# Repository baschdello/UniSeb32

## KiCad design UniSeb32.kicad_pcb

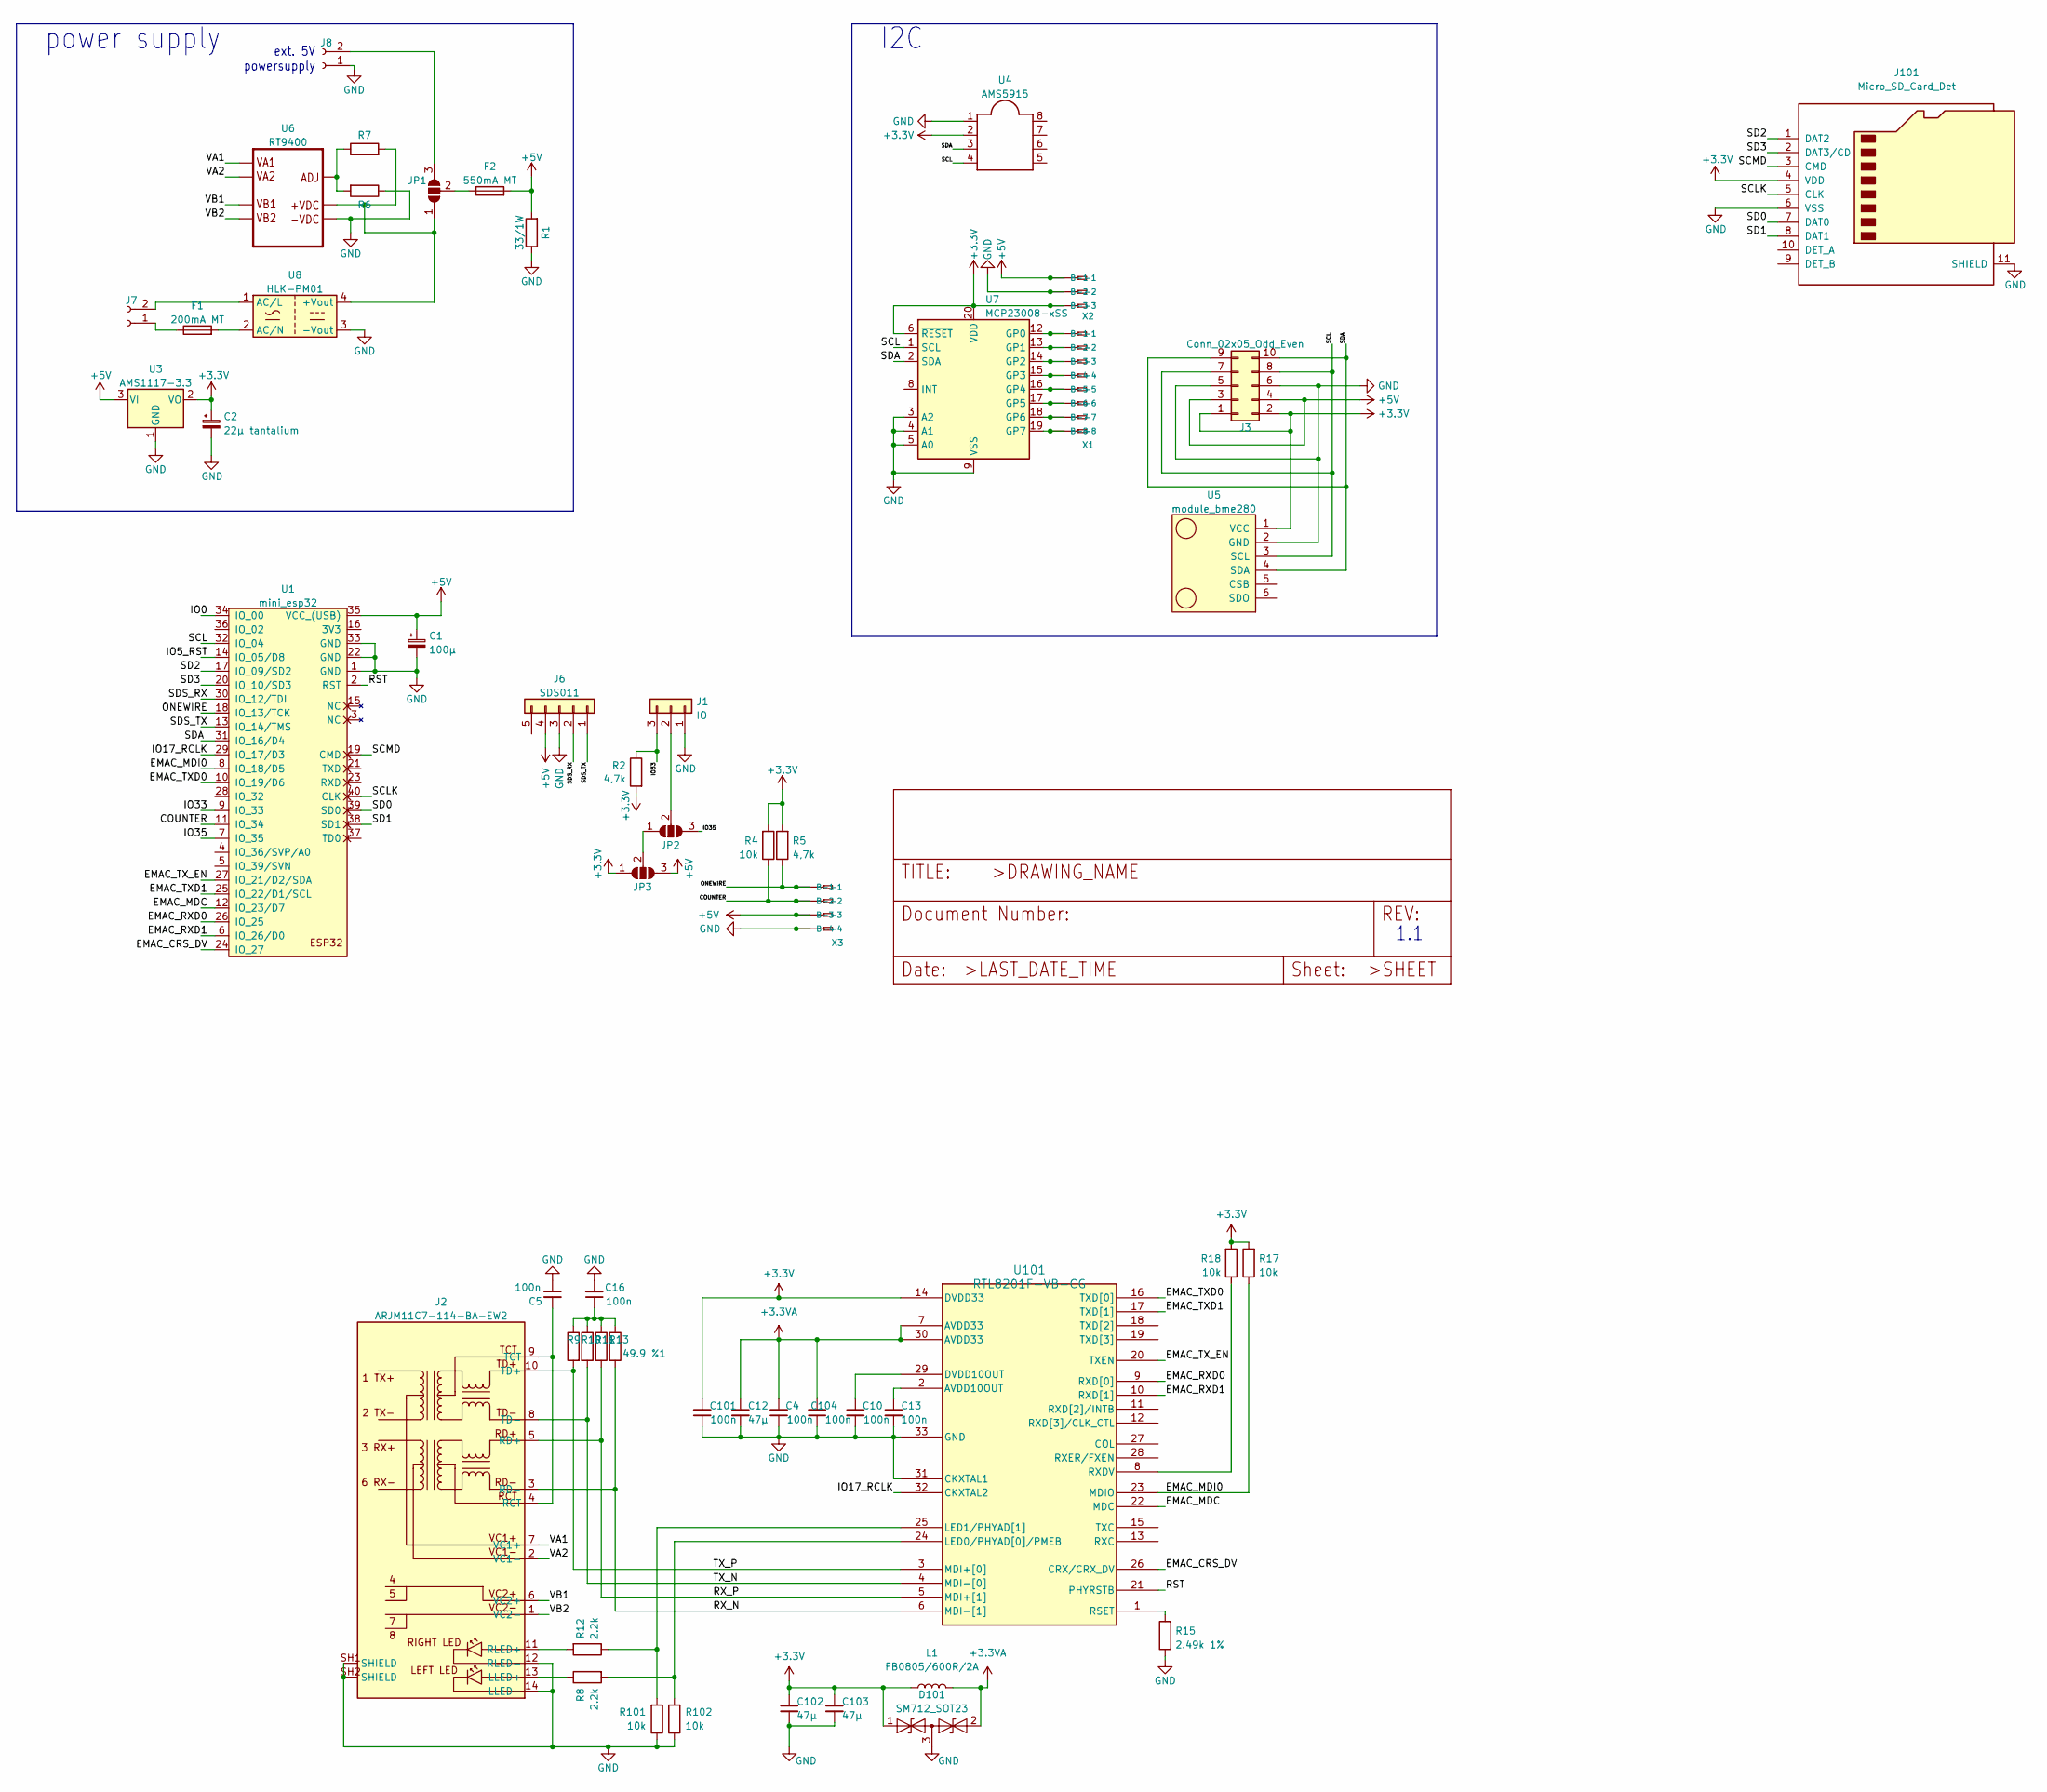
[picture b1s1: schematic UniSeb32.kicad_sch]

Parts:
C1: 100µ; CP_Radial_D5.0mm_P2.50mm
C2: 22µ tantalium; CP_Radial_D5.0mm_P2.50mm
C4, C5, C10, C13, C16, C101, C104: 100n; C_0603_1608Metric; LCSC C14663
C12, C102, C103: 47µ; C_0805_2012Metric; LCSC C2844386
D101: SM712_SOT23; SOT-23; Digikey 1655-S2303CT-ND
F1: 200mA MT; Fuse_Littelfuse_372_D8.50mm
F2: 550mA MT; Fuse_Littelfuse_372_D8.50mm
J1: IO; FanPinHeader_1x03_P2.54mm_Vertical
J2: ARJM11C7-114-BA-EW2
J3: Conn_02x05_Odd_Even; PinHeader_2x05_P2.54mm_Vertical_SMD
J6: SDS011; JST_XH_B5B-XH-A_1x05_P2.50mm_Vertical
J7, J8: Conn_01x02_Female; TerminalBlock_bornier-2_P5.08mm
J101: Micro_SD_Card_Det; microSD_HC_Hirose_DM3D-SF
JP1, JP2, JP3: SolderJumper_3_Open; SolderJumper-3_P1.3mm_Open_Pad1.0x1.5mm_NumberLabels
L1: FB0805/600R/2A; L_0805_2012Metric; LCSC C1017
R1: 33/1W; R_Axial_DIN0414_L11.9mm_D4.5mm_P5.08mm_Vertical
R2, R5: 4,7k; R_0603_1608Metric; LCSC C23162
R4: 10k; R_0603_1608Metric; JLC 0603
R6, R7: R; R_0603_1608Metric
R8, R12: 2.2k; R_0603_1608Metric; LCSC C4190
R9, R10, R11, R13: 49.9 %1; R_0603_1608Metric; LCSC C23185
R15: 2.49k 1%; R_0603_1608Metric; LCSC C203449
R17, R18, R101, R102: 10k; R_0603_1608Metric; LCSC C25804
U1: mini_esp32; ESP32_mini
U3: AMS1117-3.3; SOT-223-3_TabPin2; LCSC C6186
U4: AMS5915
U5: module_bme280
U6: RT9400
U7: MCP23008-xSS; SSOP-20_5.3x7.2mm_P0.65mm
U8: HLK-PM01; Converter_ACDC_HiLink_HLK-PMxx
U101: RTL8201F-VB-CG; QFN_8201F-VB-CG_RTK; LCSC C45044
X1: 233-508; con-wago-233-508
X2: 233-503; con-wago-233-503
X3: 233-504; con-wago-233-504

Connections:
+3.3V: C2.1, C101.2, C102.1, C103.1, D101.1 (A1), J3.1, J3.2, J101.4 (VDD), JP3.1 (A), L1.1, R2.2, R4.2, R5.2, R17.2, R18.2, U3.2 (VO), U4.2 (VCC), U5.1 (VCC), U7.6 (~RESET), U7.20 (VDD), U101.14 (DVDD33), X2.A3 (-3), X2.B3 (B-3)
+3.3VA: C4.2, C12.1, C104.2, D101.2 (A2), L1.2, U101.7 (AVDD33), U101.30 (AVDD33)
+5V: C1.1, F2.2, J3.3, J3.4, J6.4, JP3.3 (B), R1.2, U1.35 (VCC_(USB)), U3.3 (VI), X2.A1 (-1), X2.B1 (B-1), X3.A3 (-3), X3.B3 (B-3)
/COUNTER: R4.1, U1.11 (IO_34), X3.A2 (-2), X3.B2 (B-2)
/EMAC_CRS_DV: U1.24 (IO_27), U101.26 (CRX/CRX_DV)
/EMAC_MDC: U1.12 (IO_23/D7), U101.22 (MDC)
/EMAC_MDI0: R17.1, U1.8 (IO_18/D5), U101.23 (MDIO)
/EMAC_RXD0: U1.26 (IO_25), U101.9 (RXD[0])
/EMAC_RXD1: U1.6 (IO_26/D0), U101.10 (RXD[1])
/EMAC_TXD0: U1.10 (IO_19/D6), U101.16 (TXD[0])
/EMAC_TXD1: U1.25 (IO_22/D1/SCL), U101.17 (TXD[1])
/EMAC_TX_EN: U1.27 (IO_21/D2/SDA), U101.20 (TXEN)
/IO0: U1.34 (IO_00)
/IO5_RST: U1.14 (IO_05/D8)
/IO17_RCLK: U1.29 (IO_17/D3), U101.32 (CKXTAL2)
/IO33: J1.3, R2.1, U1.9 (IO_33)
/IO35: JP2.3 (B), U1.7 (IO_35)
/ONEWIRE: R5.1, U1.18 (IO_13/TCK), X3.A1 (-1), X3.B1 (B-1)
/RST: U1.2 (RST), U101.21 (PHYRSTB)
/RX_N: J2.3 (RD-), R13.2, U101.6 (MDI-[1])
/RX_P: J2.5 (RD+), R11.2, U101.5 (MDI+[1])
/SCL: J3.7, J3.8, U1.32 (IO_04), U4.4 (SCL), U5.3 (SCL), U7.1 (SCL)
/SCLK: J101.5 (CLK), U1.40 (CLK)
/SCMD: J101.3 (CMD), U1.19 (CMD)
/SD0: J101.7 (DAT0), U1.39 (SD0)
/SD1: J101.8 (DAT1), U1.38 (SD1)
/SD2: J101.1 (DAT2), U1.17 (IO_09/SD2)
/SD3: J101.2 (DAT3/CD), U1.20 (IO_10/SD3)
/SDA: J3.9, J3.10, U1.31 (IO_16/D4), U4.3 (SDA), U5.4 (SDA), U7.2 (SDA)
/SDS_RX: J6.2, U1.30 (IO_12/TDI)
/SDS_TX: J6.1, U1.13 (IO_14/TMS)
/TX_N: J2.8 (TD-), R10.2, U101.4 (MDI-[0])
/TX_P: J2.10 (TD+), R9.2, U101.3 (MDI+[0])
/VA1: J2.7 (VC1+), U6.P$1 (VA1)
/VA2: J2.2 (VC1-), U6.P$2 (VA2)
/VB1: J2.6 (VC2+), U6.P$3 (VB1)
/VB2: J2.1 (VC2-), U6.P$4 (VB2)
GND: C1.2, C2.2, C4.1, C5.1, C10.2, C12.2, C13.2, C16.2, C101.1, C102.2, C103.2, C104.1, D101.3 (common), J1.1, J2.12 (RLED-), J2.14 (LLED-), J2.SH1 (SHIELD), J2.SH2 (SHIELD), J3.5, J3.6, J6.3, J8.1, J101.6 (VSS), J101.11 (SHIELD), R1.1, R6.1, R15.1, R101.1, R102.1, U1.1 (GND), U1.22 (GND), U1.33 (GND), U3.1 (GND), U4.1 (GND), U5.2 (GND), U6.P$5 (-VDC), U7.3 (A2), U7.4 (A1), U7.5 (A0), U7.9 (VSS), U8.3 (-Vout), U101.31 (CKXTAL1), U101.33 (GND), X2.A2 (-2), X2.B2 (B-2), X3.A4 (-4), X3.B4 (B-4)
unnamed: C16.1, R9.1, R10.1, R11.1, R13.1
unnamed: J1.2, JP2.2 (C)
unnamed: J2.13 (LLED+), R8.1
unnamed: C5.2, J2.4 (RCT), J2.9 (TCT)
unnamed: J2.11 (RLED+), R12.2
unnamed: F1.1, J7.1
unnamed: J7.2, U8.1 (AC/L)
unnamed: J8.2, JP1.3 (B)
unnamed: JP1.1 (A), R7.2, U6.P$6 (+VDC), U8.4 (+Vout)
unnamed: F2.1, JP1.2 (C)
unnamed: JP2.1 (A), JP3.2 (C)
unnamed: R6.2, R7.1, U6.P$7 (ADJ)
unnamed: U7.12 (GP0), X1.A1 (-1), X1.B1 (B-1)
unnamed: U7.13 (GP1), X1.A2 (-2), X1.B2 (B-2)
unnamed: U7.14 (GP2), X1.A3 (-3), X1.B3 (B-3)
unnamed: U7.15 (GP3), X1.A4 (-4), X1.B4 (B-4)
unnamed: U7.16 (GP4), X1.A5 (-5), X1.B5 (B-5)
unnamed: U7.17 (GP5), X1.A6 (-6), X1.B6 (B-6)
unnamed: U7.18 (GP6), X1.A7 (-7), X1.B7 (B-7)
unnamed: U7.19 (GP7), X1.A8 (-8), X1.B8 (B-8)
unnamed: F1.2, U8.2 (AC/N)
unnamed: C13.1, U101.2 (AVDD10OUT)
unnamed: C10.1, U101.29 (DVDD10OUT)
unnamed: R8.2, R102.2, U101.24 (LED0/PHYAD[0]/PMEB)
unnamed: R12.1, R101.2, U101.25 (LED1/PHYAD[1])
unnamed: R15.2, U101.1 (RSET)
unnamed: R18.1, U101.8 (RXDV)

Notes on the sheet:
I2C
1.1
power supply
ext. 5V powersupply

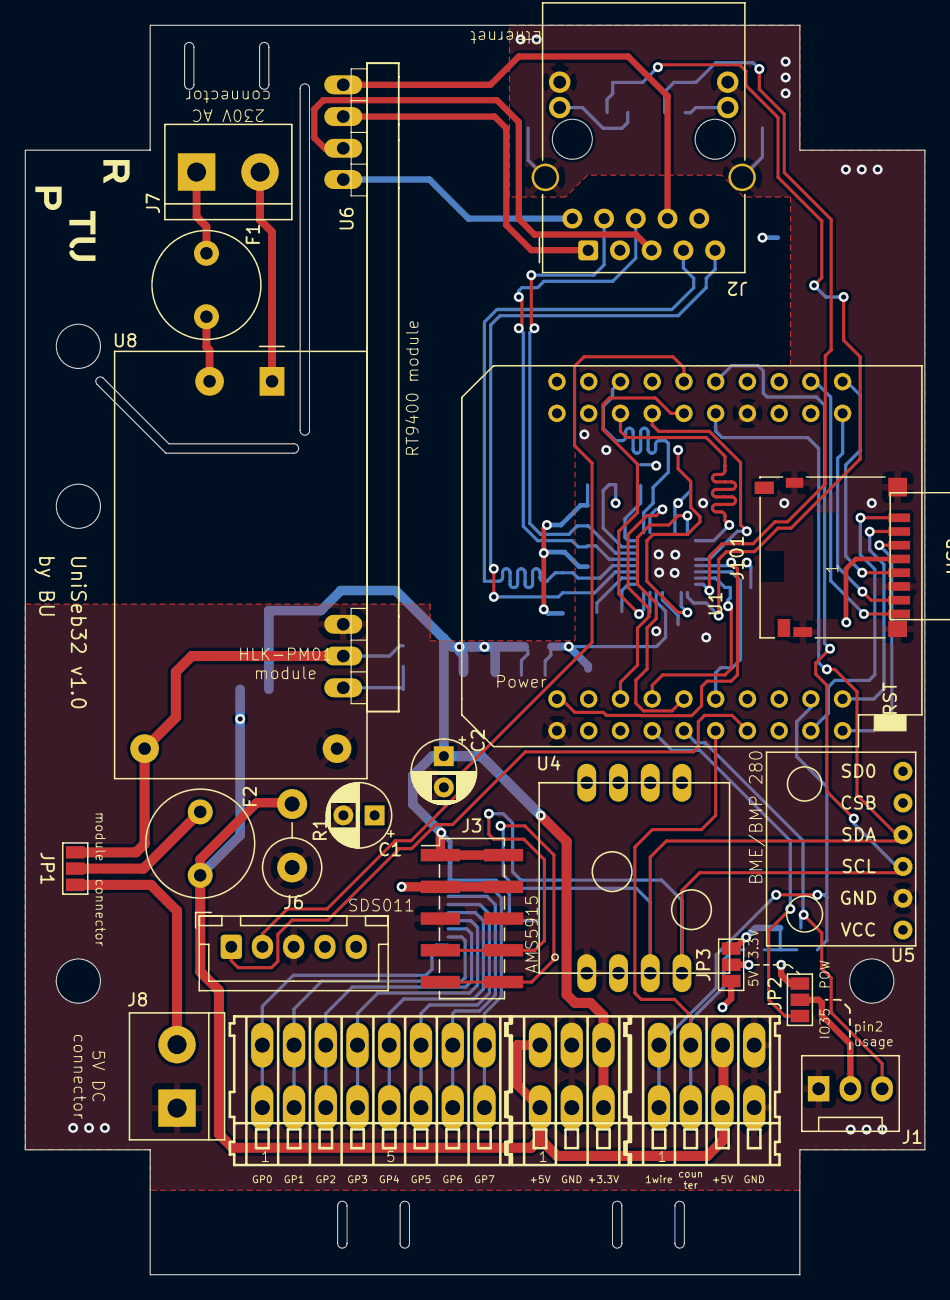
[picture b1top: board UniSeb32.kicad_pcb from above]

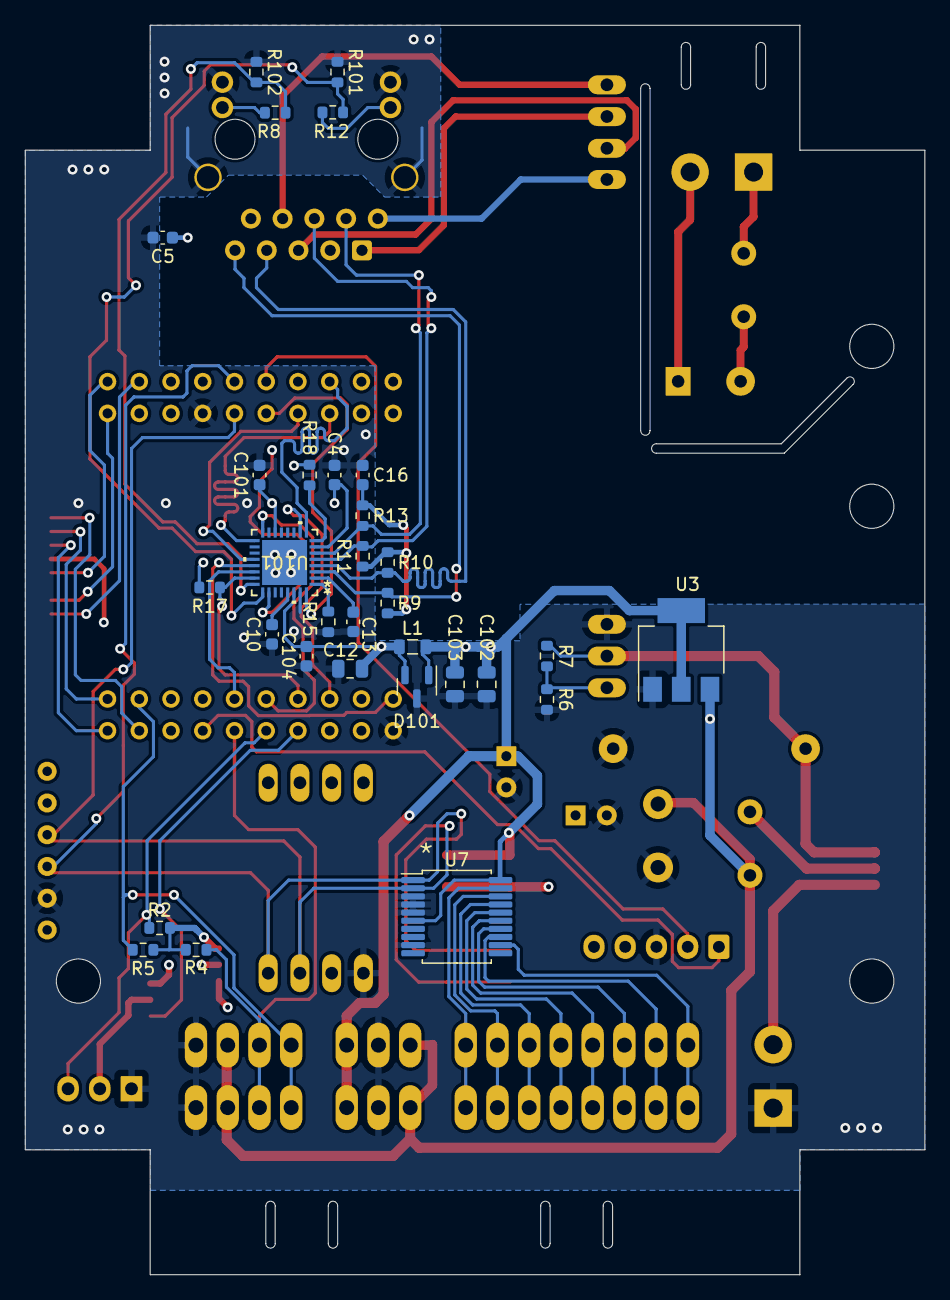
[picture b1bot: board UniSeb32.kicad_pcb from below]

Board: 4 copper layers, 72.0 x 100.0 mm, 54 parts (31 on the bottom side), 63 nets.

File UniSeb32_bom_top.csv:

"Comment","Designator","Footprint","LCSC Part #"
"100µ","C1","",""
"22µ tantalium","C2","",""
"200mA MT","F1","",""
"550mA MT","F2","",""
"IO","J1","",""
"ARJM11C7-114-BA-EW2","J2","",""
"Conn_02x05_Odd_Even","J3","",""
"SDS011","J6","",""
"Conn_01x02_Female","J7 J8","",""
"SolderJumper_2_Open","JP1","",""
"SolderJumper_3_Open","JP2","",""
"33/1W","R1","",""
"mini_esp32","U1","",""
"AMS5919","U4","",""
"module_bme280","U5","",""
"RT9400","U6","",""
"HLK-PM01","U8","",""
"233-508","X1","",""
"233-503","X2","",""
"233-504","X3","",""

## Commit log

2023-01-23 initial
2023-05-15 switched to 4 layer PCB. Routed remaining airwires
2023-08-10 Added attributes for jlcpcb assembly
2023-09-05 Fixes wrong pin numbering at Y1
2023-09-12 corrected mapping of pins added SD slot removed crystal y1 and capacitors in bom and cpl file
2024-02-21 Changed PHY to RTL8201F
2024-03-04 finished routing
2024-06-06 removed SJ1, rename SJ2 -> SJ1, added SJ2 to change pin2 usage of J1
2024-06-06 added pullup for pin3 of J1
2024-06-24 Changed JP2-fixed voltage option (3.3V) to flexible voltage (3.3V/5V) with JP3
2024-08-01 changed via type near C101
2026-03-05 ESP32 und Power-Module verschoben wegen Gehäuseabmessungen
